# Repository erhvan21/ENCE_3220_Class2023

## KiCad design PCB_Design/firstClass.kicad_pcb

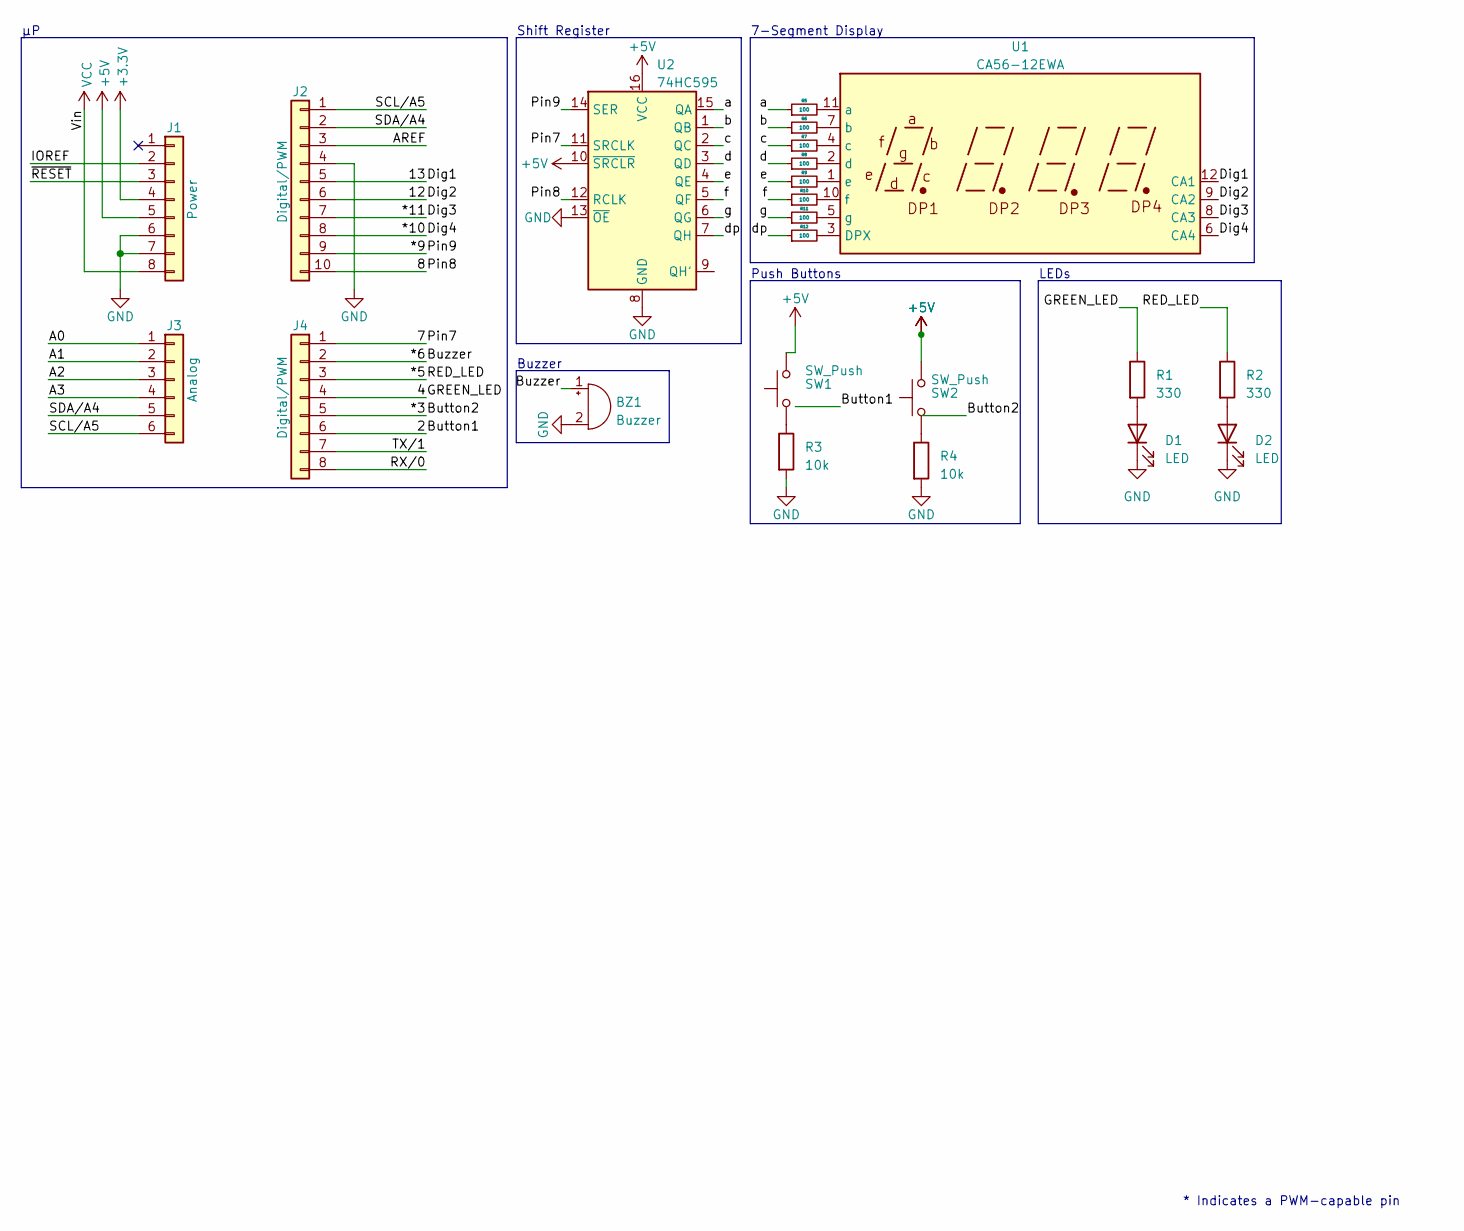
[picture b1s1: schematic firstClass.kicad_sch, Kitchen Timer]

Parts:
BZ1: Buzzer; Buzzer_15x7.5RM7.6
D1, D2: LED; LED_D5.0mm
J1: Power; PinSocket_1x08_P2.54mm_Vertical
J2: Digital/PWM; PinSocket_1x10_P2.54mm_Vertical
J3: Analog; PinSocket_1x06_P2.54mm_Vertical
J4: Digital/PWM; PinSocket_1x08_P2.54mm_Vertical
R1, R2: 330; R_Axial_DIN0207_L6.3mm_D2.5mm_P7.62mm_Horizontal
R3, R4: 10k; R_Axial_DIN0207_L6.3mm_D2.5mm_P7.62mm_Horizontal
R5, R6, R7, R8, R9, R10, R11, R12: 100; R_Axial_DIN0207_L6.3mm_D2.5mm_P7.62mm_Horizontal
SW1, SW2: SW_Push; SW_PUSH_6mm
U1: CA56-12EWA
U2: 74HC595

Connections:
+3V3: J1.4
+5V: J1.5, SW1.2, SW2.2, U2.10 (~SRCLR), U2.16 (VCC)
/2: J4.6
/4: J4.4, R1.1
/7: J4.1, U2.11 (SRCLK)
/8: J2.10, U2.12 (RCLK)
/12: J2.6, U1.9 (CA2)
/13: J2.5, U1.12 (CA1)
/*3: J4.5
/*5: J4.3, R2.1
/*6: BZ1.1 (-), J4.2
/*9: J2.9, U2.14 (SER)
/*10: J2.8, U1.6 (CA4)
/*11: J2.7, U1.8 (CA3)
/A0: J3.1
/A1: J3.2
/A2: J3.3
/A3: J3.4
/AREF: J2.3
/IOREF: J1.2
/RX/0: J4.8
/SCL/A5: J2.1, J3.6
/SDA/A4: J2.2, J3.5
/TX/1: J4.7
/a: R5.1, U2.15 (QA)
/b: R6.1, U2.1 (QB)
/c: R7.1, U2.2 (QC)
/d: R8.1, U2.3 (QD)
/dp: R12.1, U2.7 (QH)
/e: R9.1, U2.4 (QE)
/f: R10.1, U2.5 (QF)
/g: R11.1, U2.6 (QG)
/~RESET: J1.3
GND: BZ1.2 (+), D1.1 (K), D2.1 (K), J1.6, J1.7, J2.4, R3.2, R4.2, U2.8 (GND), U2.13 (~OE)
unnamed: D1.2 (A), R1.2
unnamed: D2.2 (A), R2.2
unnamed: R3.1, SW1.1
unnamed: R4.1, SW2.1
unnamed: R12.2, U1.3 (DPX)
unnamed: R5.2, U1.11 (a)
unnamed: R6.2, U1.7 (b)
unnamed: R7.2, U1.4 (c)
unnamed: R8.2, U1.2 (d)
unnamed: R9.2, U1.1 (e)
unnamed: R10.2, U1.10 (f)
unnamed: R11.2, U1.5 (g)
VCC: J1.8

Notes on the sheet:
LEDs
Push Buttons
Shift Register
* Indicates a PWM-capable pin
7-Segment Display
Buzzer

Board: 2 copper layers, 22 parts (0 on the bottom side), 23 nets, no tracks yet.

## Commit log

2023-04-07 Final Arduino Timer Code
2023-04-07 gerber files
2023-04-13 Notes
    added block diagrams for notes
